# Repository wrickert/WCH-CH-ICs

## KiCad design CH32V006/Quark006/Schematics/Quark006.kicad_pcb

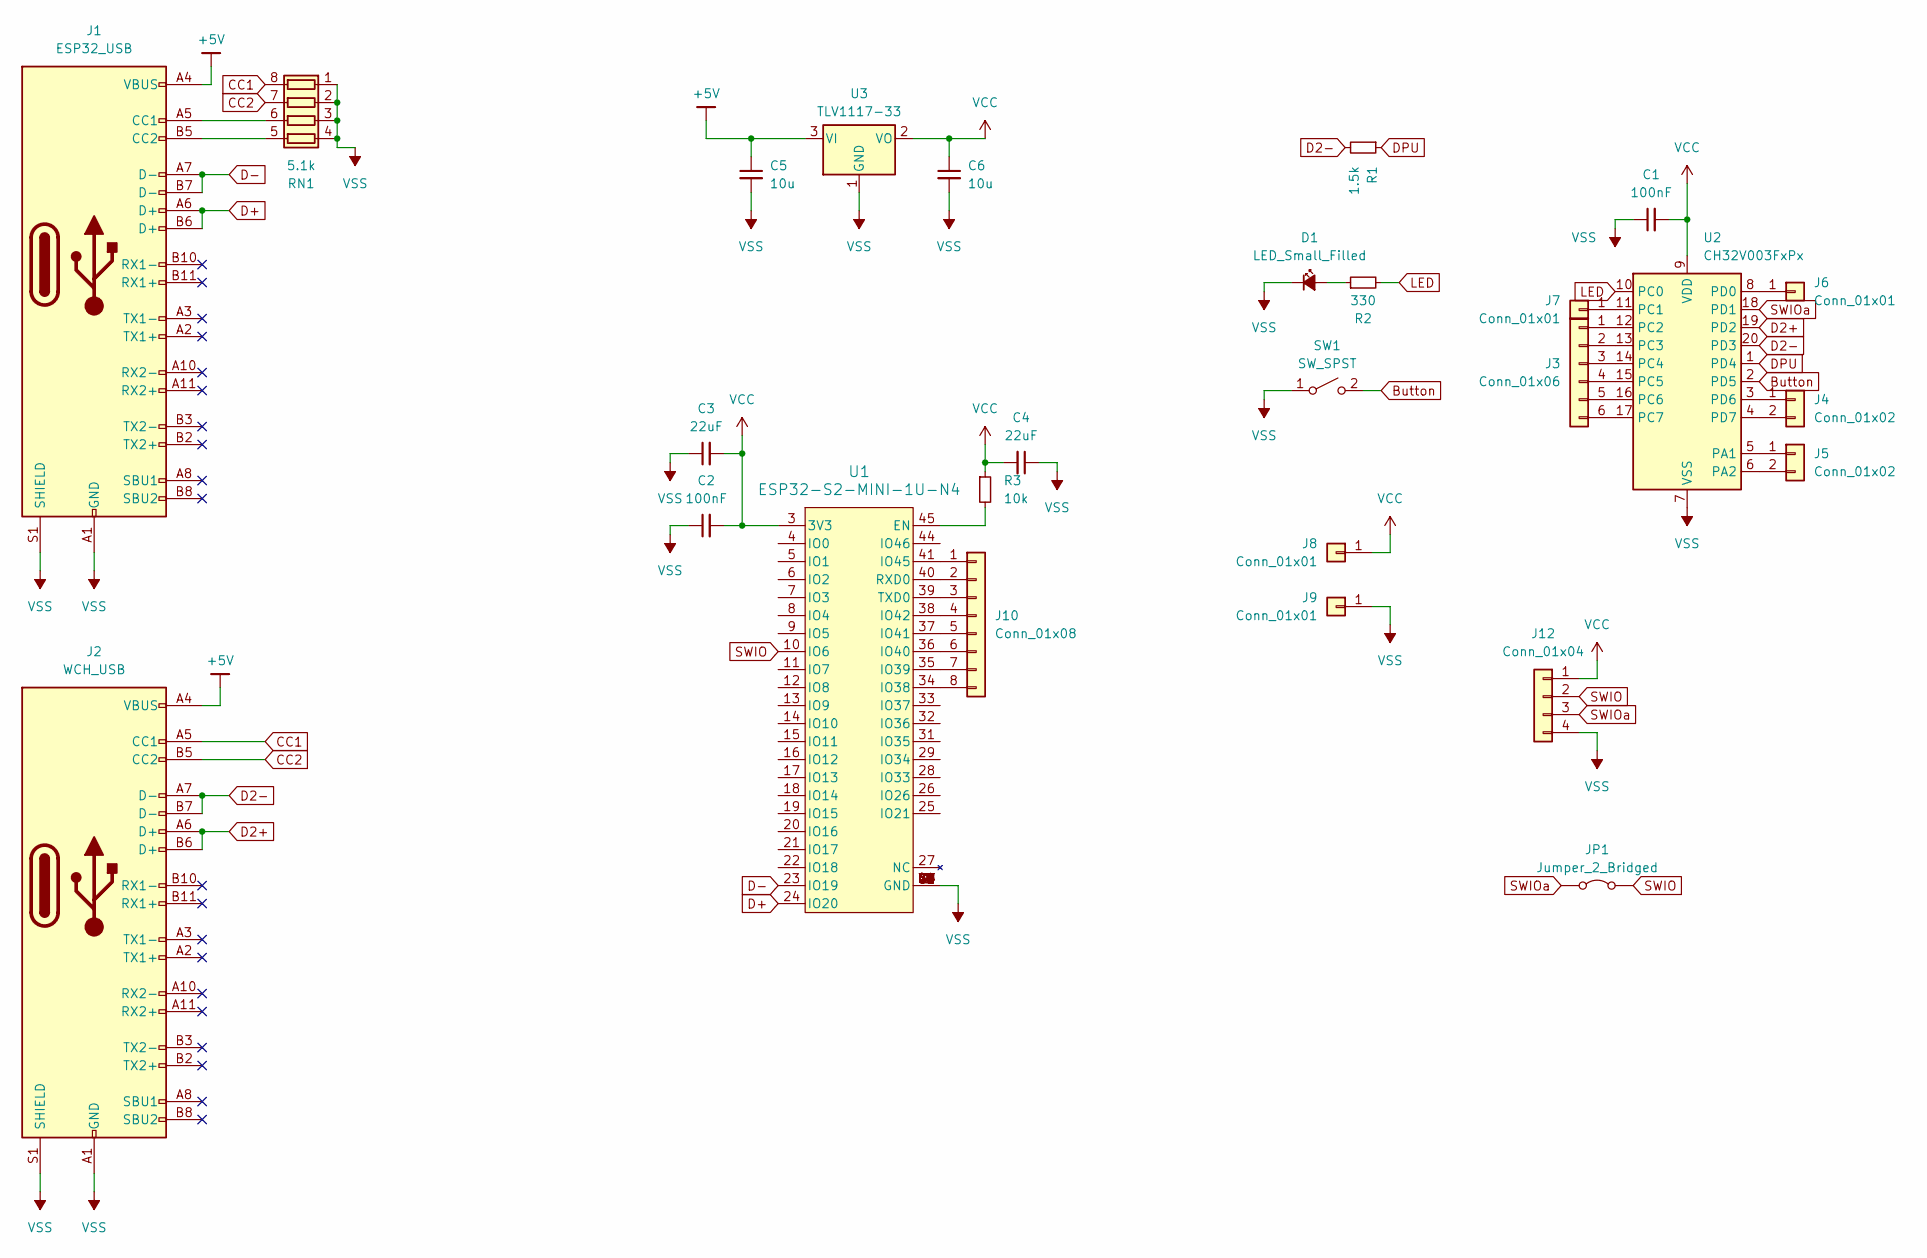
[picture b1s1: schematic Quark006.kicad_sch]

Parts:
C1, C2: 100nF; C_0805_2012Metric
C3, C4: 22uF; C_0805_2012Metric
C5, C6: 10u; C_0805_2012Metric
D1: LED_Small_Filled; LED_0805_2012Metric
J1: ESP32_USB; USB_C_Receptical-Jing
J2: WCH_USB; USB_C_Receptical-Jing
J3: Conn_01x06; PinHeader_1x06_P2.54mm_Vertical
J4, J5: Conn_01x02; PinHeader_1x02_P2.54mm_Vertical
J6, J7, J8, J9: Conn_01x01; PinHeader_1x01_P2.54mm_Vertical
J10: Conn_01x08; PinHeader_1x08_P1.00mm_Vertical
J12: Conn_01x04; PinHeader_1x04_P2.54mm_Vertical
JP1: Jumper_2_Bridged; SolderJumper-2_P1.3mm_Bridged_RoundedPad1.0x1.5mm
R1: 1.5k; R_0805_2012Metric
R2: 330; R_0805_2012Metric
R3: 10k; R_0805_2012Metric
RN1: 5.1k; R_Array_Convex_4x0603
SW1: SW_SPST; TS3315A
U1: ESP32-S2-MINI-1U-N4; ESP32-S2-MINI-1U_EXP
U2: CH32V003FxPx; TSSOP-20_4.4x6.5mm_P0.65mm
U3: TLV1117-33; SOT-223-3_TabPin2

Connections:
+5V: C5.1, J1.A4 (VBUS), J1.A9 (VBUS), J1.B4 (VBUS), J1.B9 (VBUS), J2.A4 (VBUS), J2.A9 (VBUS), J2.B4 (VBUS), J2.B9 (VBUS), U3.3 (VI)
Button: SW1.2 (B), U2.2 (PD5)
CC1: J2.A5 (CC1), RN1.8 (R1.2)
CC2: J2.B5 (CC2), RN1.7 (R2.2)
D2+: J2.A6 (D+), J2.B6 (D+), U2.19 (PD2)
D2-: J2.A7 (D-), J2.B7 (D-), R1.2, U2.20 (PD3)
D+: J1.A6 (D+), J1.B6 (D+), U1.24 (IO20)
D-: J1.A7 (D-), J1.B7 (D-), U1.23 (IO19)
DPU: R1.1, U2.1 (PD4)
LED: R2.2, U2.10 (PC0)
unnamed: D1.2 (A), R2.1
unnamed: J1.A5 (CC1), RN1.6 (R3.2)
unnamed: J1.B5 (CC2), RN1.5 (R4.2)
unnamed: J3.1, U2.12 (PC2)
unnamed: J3.2, U2.13 (PC3)
unnamed: J3.3, U2.14 (PC4)
unnamed: J3.4, U2.15 (PC5)
unnamed: J3.5, U2.16 (PC6)
unnamed: J3.6, U2.17 (PC7)
unnamed: J4.1, U2.3 (PD6)
unnamed: J4.2, U2.4 (PD7)
unnamed: J5.1, U2.5 (PA1)
unnamed: J5.2, U2.6 (PA2)
unnamed: J6.1, U2.8 (PD0)
unnamed: J7.1, U2.11 (PC1)
unnamed: J10.1, U1.41 (IO45)
unnamed: J10.2, U1.40 (RXD0)
unnamed: J10.3, U1.39 (TXD0)
unnamed: J10.4, U1.38 (IO42)
unnamed: J10.5, U1.37 (IO41)
unnamed: J10.6, U1.36 (IO40)
unnamed: J10.7, U1.35 (IO39)
unnamed: J10.8, U1.34 (IO38)
unnamed: R3.2, U1.45 (EN)
SWIO: J12.2, JP1.2 (B), U1.10 (IO6)
SWIOa: J12.3, JP1.1 (A), U2.18 (PD1)
VCC: C1.2, C2.2, C3.2, C4.2, C6.1, J8.1, J12.1, R3.1, U1.3 (3V3), U2.9 (VDD), U3.2 (VO)
VSS: C1.1, C2.1, C3.1, C4.1, C5.2, C6.2, D1.1 (K), J1.A1 (GND), J1.A12 (GND), J1.B1 (GND), J1.B12 (GND), J1.S1 (SHIELD), J2.A1 (GND), J2.A12 (GND), J2.B1 (GND), J2.B12 (GND), J2.S1 (SHIELD), J9.1, J12.4, RN1.1 (R1.1), RN1.2 (R2.1), RN1.3 (R3.1), RN1.4 (R4.1), SW1.1 (A), U1.1 (GND), U1.2 (GND), U1.30 (GND), U1.42 (GND), U1.43 (GND), U1.46 (GND), U1.47 (GND), U1.48 (GND), U1.49 (GND), U1.50 (GND), U1.51 (GND), U1.52 (GND), U1.53 (GND), U1.54 (GND), U1.55 (GND), U1.56 (GND), U1.57 (GND), U1.58 (GND), U1.59 (GND), U1.60 (GND), U1.61 (GND), U1.62 (GND), U1.63 (GND), U1.64 (GND), U1.65 (GND), U1.66 (GND), U1.67 (GND), U1.68 (GND), U1.69 (GND), U1.70 (GND), U1.71 (GND), U1.72 (GND), U1.73 (GND), U2.7 (VSS), U3.1 (GND)

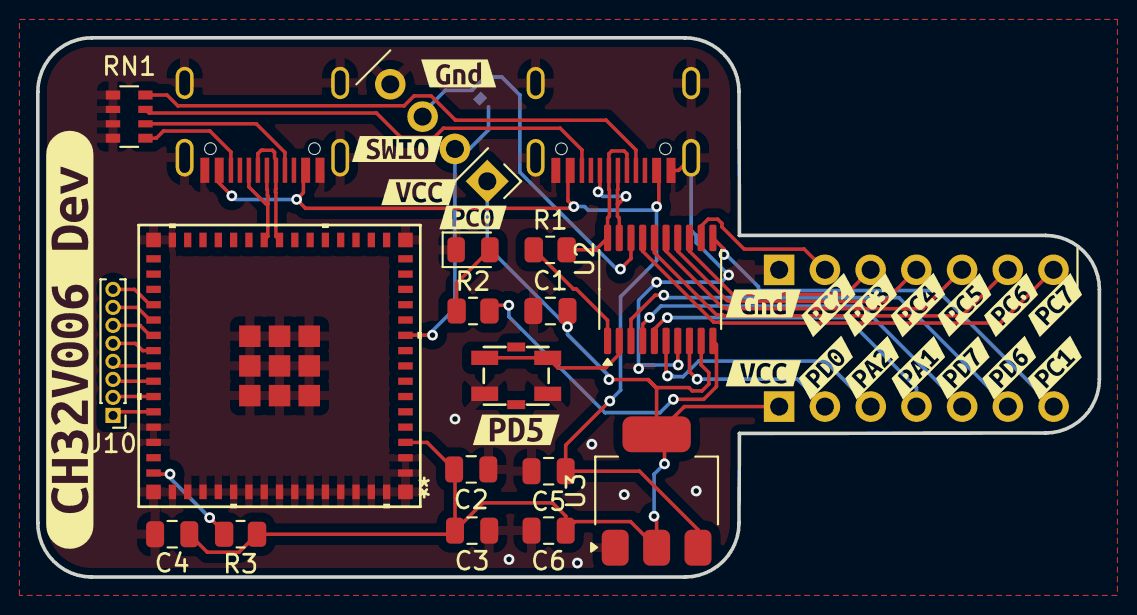
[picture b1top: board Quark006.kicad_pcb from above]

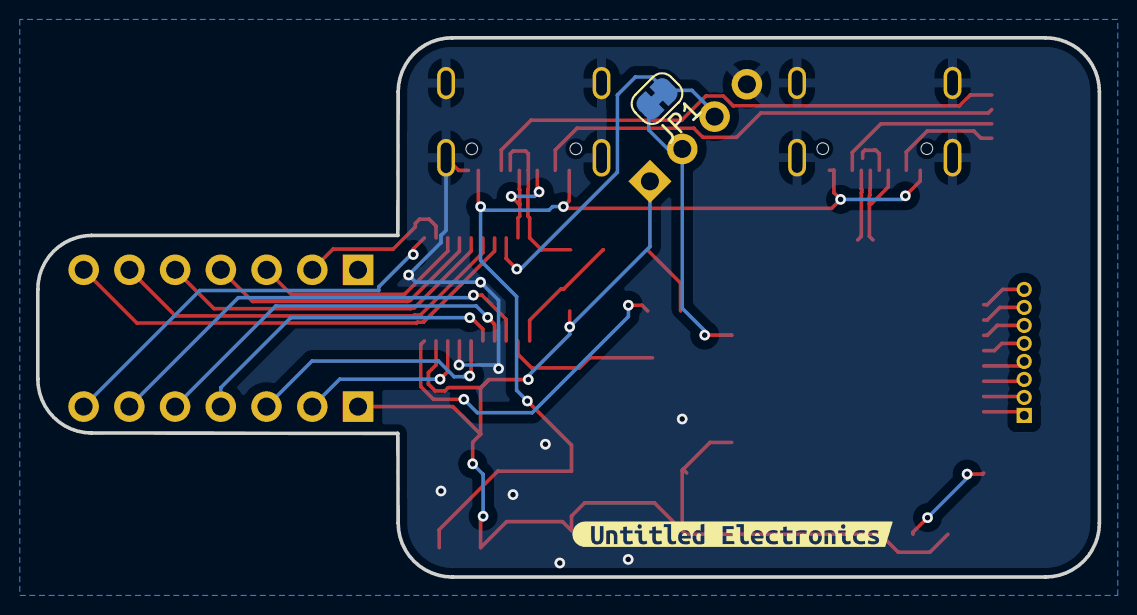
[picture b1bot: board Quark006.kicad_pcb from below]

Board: 2 copper layers, 59.0 x 30.0 mm, 48 parts (2 on the bottom side), 38 nets.

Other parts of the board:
kibuzzard-67AFB7A0: G***; kibuzzard-67AFB7A0
kibuzzard-67AFB7A5: G***; kibuzzard-67AFB7A5
kibuzzard-67AFB7AA: G***; kibuzzard-67AFB7AA
kibuzzard-67AFB7B7: G***; kibuzzard-67AFB7B7
kibuzzard-67AFB7C4: G***; kibuzzard-67AFB7C4
kibuzzard-67AFB7CD: G***; kibuzzard-67AFB7CD
kibuzzard-67AFB7D5: G***; kibuzzard-67AFB7D5
kibuzzard-67AFB7DD: G***; kibuzzard-67AFB7DD
kibuzzard-67AFB7E3: G***; kibuzzard-67AFB7E3
kibuzzard-67AFB7EB: G***; kibuzzard-67AFB7EB
kibuzzard-67AFB7F1: G***; kibuzzard-67AFB7F1
kibuzzard-67AFB7F8, kibuzzard-67AFB7F8#2: G***; kibuzzard-67AFB7F8
kibuzzard-67AFB81A: G***; kibuzzard-67AFB81A
kibuzzard-67AFB799: G***; kibuzzard-67AFB799
kibuzzard-67AFBA81: G***; kibuzzard-67AFBA81
kibuzzard-67AFBDD6: G***; kibuzzard-67AFBDD6
kibuzzard-67AFBE16: G***; kibuzzard-67AFBE16
kibuzzard-67B101C4: G***; kibuzzard-67B101C4
kibuzzard-67B102C6: G***; kibuzzard-67B102C6
kibuzzard-67B10245: G***; kibuzzard-67B10245

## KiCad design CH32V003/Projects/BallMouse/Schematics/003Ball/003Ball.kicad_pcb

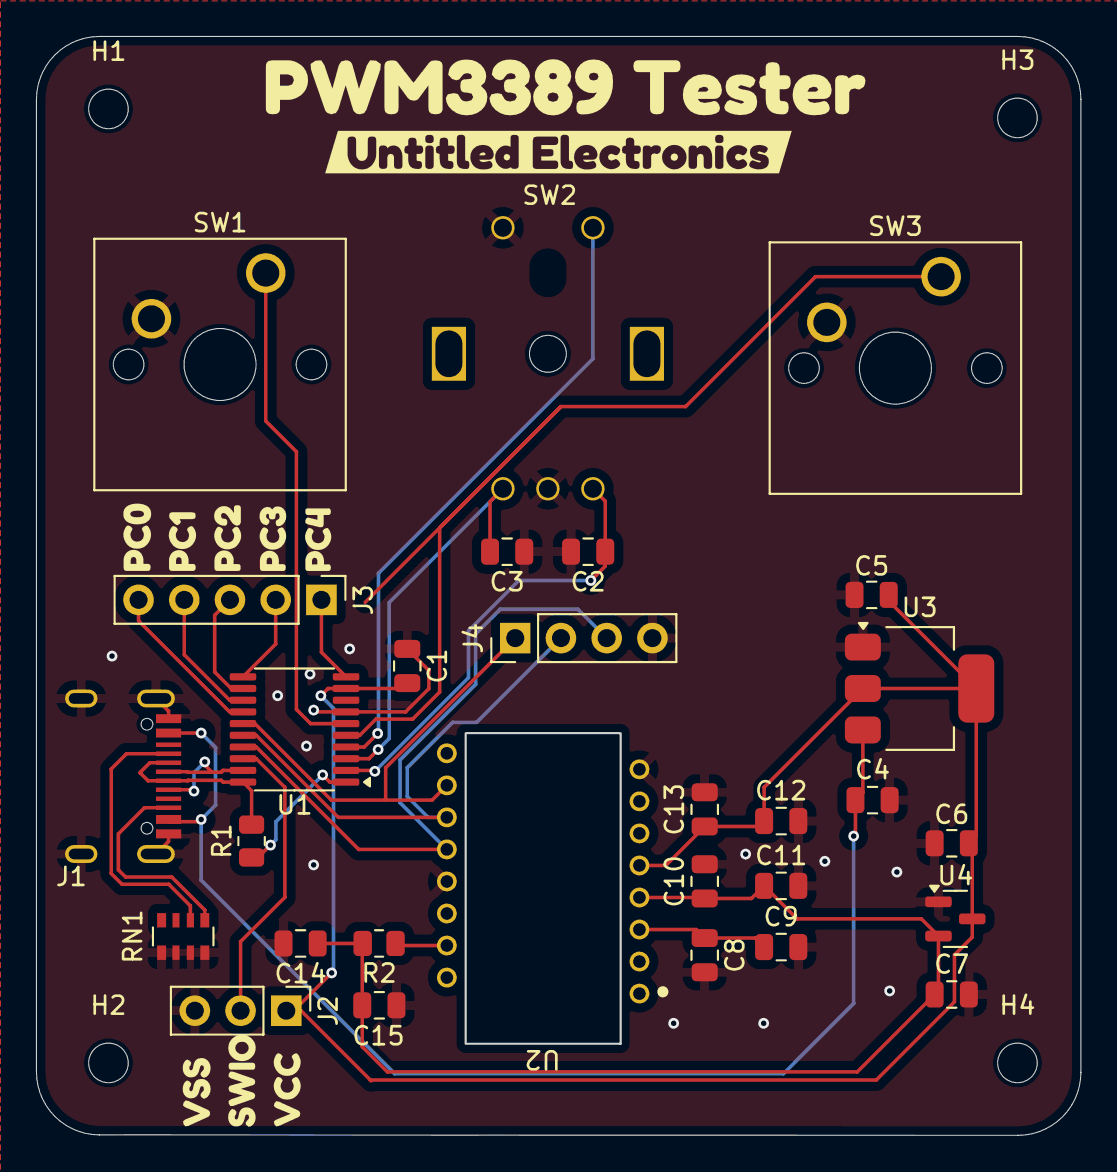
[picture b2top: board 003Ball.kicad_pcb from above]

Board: 2 copper layers, 58.0 x 61.1 mm, 37 parts (0 on the bottom side), 25 nets.

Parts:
C1, C2, C3, C9, C10, C12, C14: 100nF; C_0805_2012Metric
C4, C5: 10u; C_0805_2012Metric
C6, C7: 1uF; C_0805_2012Metric
C8: 4.7uF; C_0805_2012Metric
C11, C13, C15: 10uF; C_0805_2012Metric
H1, H2, H3, H4: MountingHole; MountingHole_2.2mm_M2
J1: USB_C_Receptacle; USB_C_Receptical-Jing
J2: Prog; PinHeader_1x03_P2.54mm_Vertical
J3: Conn_01x05; PinHeader_1x05_P2.54mm_Vertical
J4: Conn_01x04; PinHeader_1x04_P2.54mm_Vertical
R1: 1.5k; R_0805_2012Metric
R2: 13; R_0805_2012Metric
RN1: 5.1k; R_Array_Convex_4x0603
SW1, SW3: SW_Push_45deg; SW_Cherry_MX_1.00u_PCB
SW2: Rotary_Encoder_Switch; EC11L1524E03_Rotary_Encoder
U1: CH32V003FxPx; TSSOP-20_4.4x6.5mm_P0.65mm
U2: PWM3389; PMW3389
U3: TLV1117-33; SOT-223-3_TabPin2
U4: TLV1117-18; SOT-23
kibuzzard-67733B6F: G***; kibuzzard-67733B6F
kibuzzard-67733BE6: G***; kibuzzard-67733BE6
kibuzzard-67733C4A: G***; kibuzzard-67733C4A
kibuzzard-67733C22: G***; kibuzzard-67733C22

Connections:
+1V8: C7.1, C10.1, C11.1, C14.1, C15.1, R2.2, U2.4 (VCC), U4.2 (VO)
+5V: C4.1, J1.A4 (VBUS), J1.A9 (VBUS), J1.B4 (VBUS), J1.B9 (VBUS), U3.3 (VI)
/RotaryA: C2.1, SW2.B, U1.2 (PD5)
/RotaryB: C3.2, SW2.A, U1.3 (PD6)
/RotaryS: SW2.S2, U1.4 (PD7)
D+: J1.A6 (D+), J1.B6 (D+), U1.19 (PD2)
D-: J1.A7 (D-), J1.B7 (D-), R1.2, U1.20 (PD3)
DPU: R1.1, U1.1 (PD4)
Left: SW1.1, U1.6 (PA2)
MISO: J4.3, U1.17 (PC7), U2.12 (MISO)
MOSI: J4.2, U1.16 (PC6), U2.11 (MOSI)
unnamed: J1.A5 (CC1), RN1.6 (R3.2)
unnamed: J1.B5 (CC2), RN1.5 (R4.2)
unnamed: J3.1, U1.10 (PC0)
unnamed: J3.2, U1.11 (PC1)
unnamed: J3.3, U1.12 (PC2)
unnamed: J3.4, U1.13 (PC3)
unnamed: J3.5, U1.14 (PC4)
unnamed: R2.1, U2.15 (LED)
unnamed: C8.1, C9.1, U2.3 (VDCPix)
Right: SW3.1, U1.5 (PA1)
SCLK: J4.1, U1.15 (PC5), U2.10 (SCLK)
SWIO: J2.2, U1.18 (PD1)
VCC: C1.2, C5.1, C6.1, C12.1, C13.1, J2.1, U1.9 (VDD), U2.5 (VDDIO), U3.2 (VO), U4.3 (VI)
VSS: C1.1, C2.2, C3.1, C4.2, C5.2, C6.2, C7.2, C8.2, C9.2, C10.2, C11.2, C12.2, C13.2, C14.2, C15.2, J1.A1 (GND), J1.A12 (GND), J1.B1 (GND), J1.B12 (GND), J1.S1 (SHIELD), J2.3, J4.4, RN1.1 (R1.1), RN1.2 (R2.1), RN1.3 (R3.1), RN1.4 (R4.1), SW1.2, SW2.C, SW2.S1, SW3.2, U1.7 (VSS), U2.8 (VSS), U2.13 (NCS), U3.1 (GND), U4.1 (GND)

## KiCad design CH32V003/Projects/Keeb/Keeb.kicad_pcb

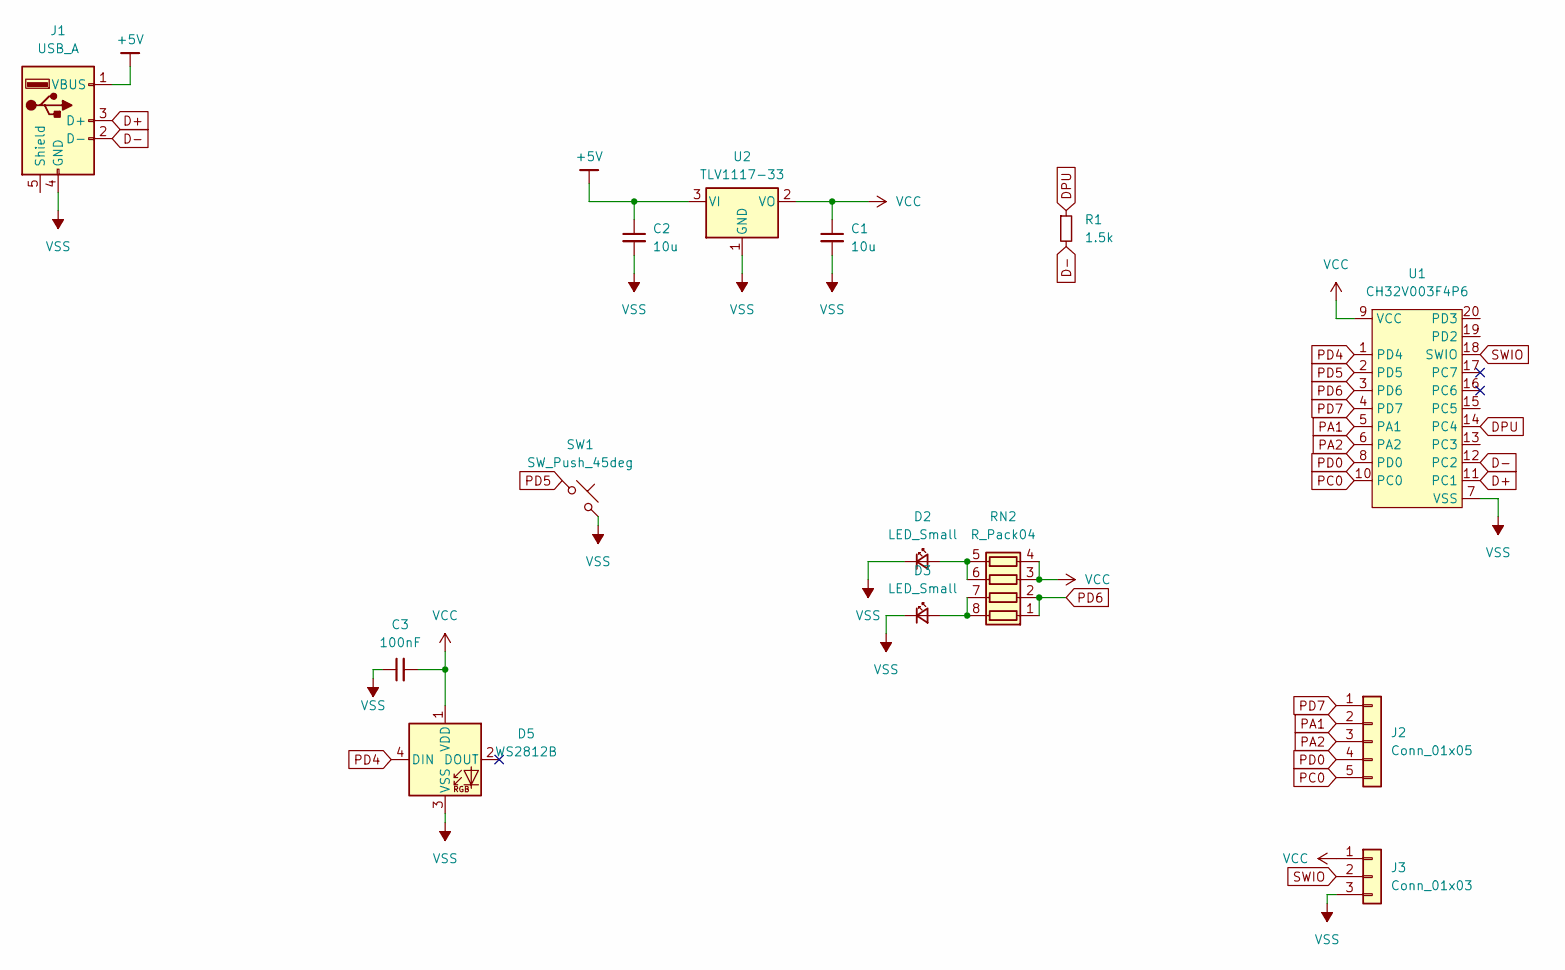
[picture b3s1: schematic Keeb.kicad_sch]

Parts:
C1, C2: 10u; C_0805_2012Metric
C3: 100nF; C_0805_2012Metric
D2, D3: LED_Small; LED_0805_2012Metric
D5: WS2812B; SK6812-E_Reverse
J1: USB_A; CONN-USB-A-PCB-TRACES
J2: Conn_01x05; PinHeader_1x05_P2.54mm_Vertical
J3: Conn_01x03; PinHeader_1x03_P2.54mm_Vertical
R1: 1.5k; R_0805_2012Metric
RN2: R_Pack04; R_Array_Convex_4x0603
SW1: SW_Push_45deg; SW_Cherry_MX_1.00u_PCB
U1: CH32V003F4P6; TSSOP-20_4.4x6.5mm_P0.65mm
U2: TLV1117-33; SOT-23-3

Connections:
+5V: C2.1, J1.1 (VBUS), U2.3 (VI)
D+: J1.3 (D+), U1.11 (PC1)
D-: J1.2 (D-), R1.2, U1.12 (PC2)
DPU: R1.1, U1.14 (PC4)
unnamed: D2.2 (A), RN2.5 (R4.2), RN2.6 (R3.2)
unnamed: D3.2 (A), RN2.7 (R2.2), RN2.8 (R1.2)
PA1: J2.2, U1.5 (PA1)
PA2: J2.3, U1.6 (PA2)
PC0: J2.5, U1.10 (PC0)
PD0: J2.4, U1.8 (PD0)
PD4: D5.4 (DIN), U1.1 (PD4)
PD5: SW1.1, U1.2 (PD5)
PD6: RN2.1 (R1.1), RN2.2 (R2.1), U1.3 (PD6)
PD7: J2.1, U1.4 (PD7)
SWIO: J3.2, U1.18 (SWIO)
VCC: C1.1, C3.2, D5.1 (VDD), J3.1, RN2.3 (R3.1), RN2.4 (R4.1), U1.9 (VCC), U2.2 (VO)
VSS: C1.2, C2.2, C3.1, D2.1 (K), D3.1 (K), D5.3 (VSS), J1.4 (GND), J3.3, SW1.2, U1.7 (VSS), U2.1 (GND)

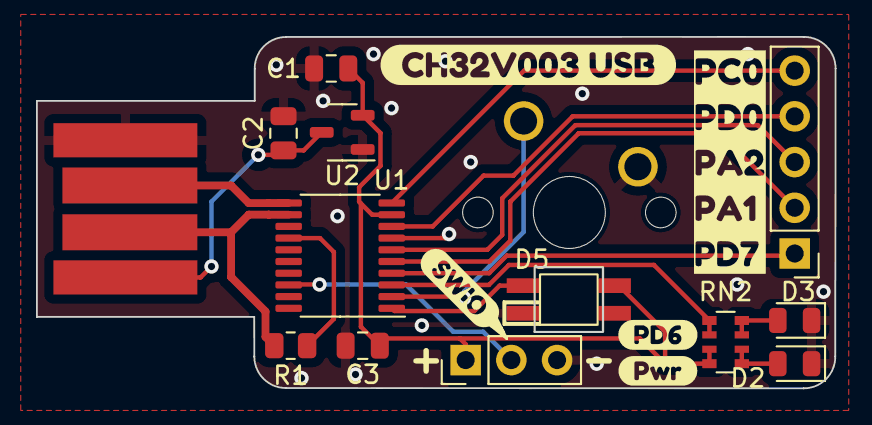
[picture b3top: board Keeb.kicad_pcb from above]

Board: 2 copper layers, 44.4 x 19.5 mm, 19 parts (1 on the bottom side), 17 nets.

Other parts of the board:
kibuzzard-65C27C9E: G***; kibuzzard-65C27C9E
kibuzzard-65C27C56: G***; kibuzzard-65C27C56
kibuzzard-65C27CA6: G***; kibuzzard-65C27CA6
kibuzzard-65C27CFD: G***; kibuzzard-65C27CFD
kibuzzard-65C28AFE: G***; kibuzzard-65C28AFE

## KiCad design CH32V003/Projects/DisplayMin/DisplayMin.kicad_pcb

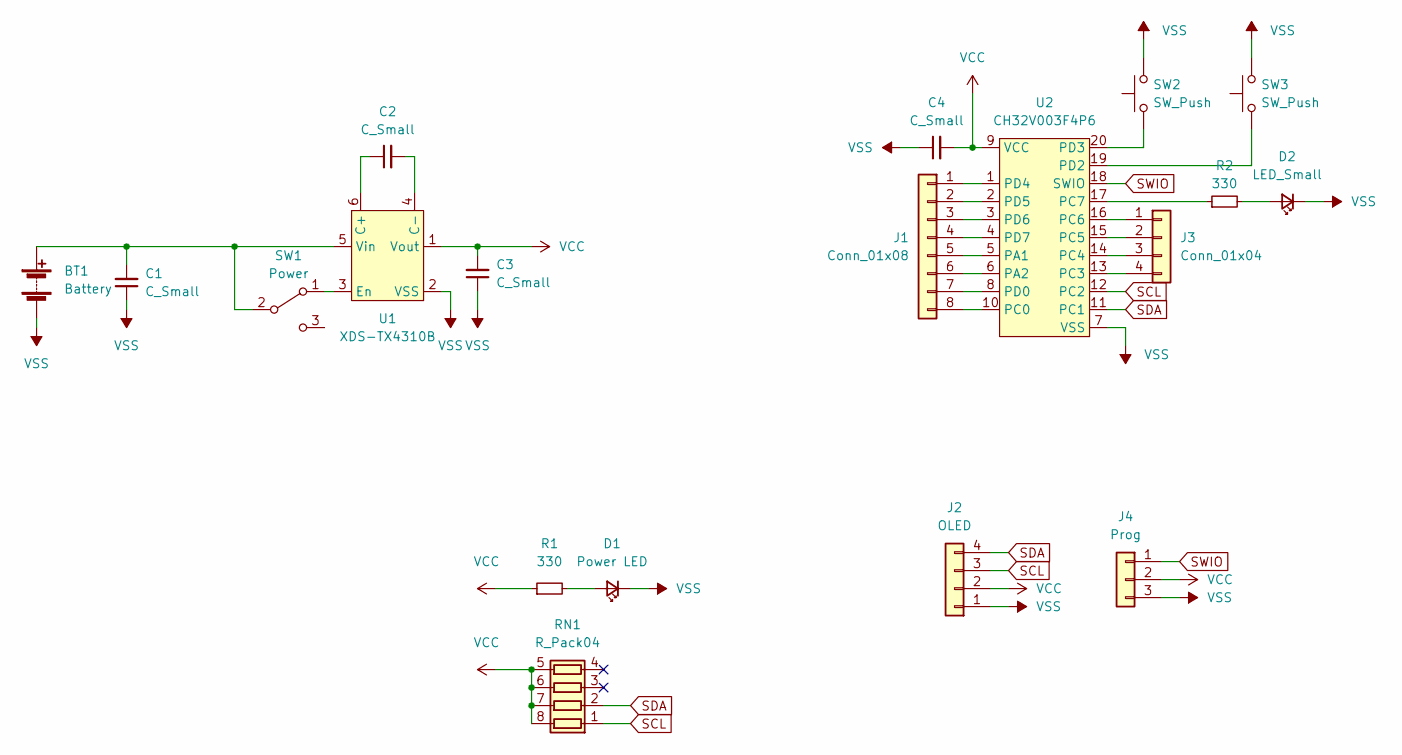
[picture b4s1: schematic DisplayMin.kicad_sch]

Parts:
BT1: Battery; Keystone_1012_2AA_SMD_UE
C1, C2, C3, C4: C_Small; C_0805_2012Metric
D1: Power LED; LED_0805_2012Metric
D2: LED_Small; LED_0805_2012Metric
J1: Conn_01x08; PinHeader_1x08_P2.54mm_Vertical
J2: OLED; PinHeader_1x04_P2.54mm_Vertical
J3: Conn_01x04; PinHeader_1x04_P2.54mm_Vertical
J4: Prog; PinHeader_1x03_P2.54mm_Vertical
R1, R2: 330; R_0805_2012Metric
RN1: R_Pack04; R_Array_Concave_4x0603
SW1: Power; SK-3296S_switch
SW2: SW_Push; SW_SPST_EVQP0
SW3: SW_Push; SW_Cherry_MX_1.00u_PCB
U1: XDS-TX4310B; SOT-23-6
U2: CH32V003F4P6; SSOP-20_4.4x6.5mm_P0.65mm

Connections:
unnamed: BT1.1 (+), C1.2, SW1.2 (B), U1.5 (Vin)
unnamed: C2.1, U1.6 (C+)
unnamed: C2.2, U1.4 (C-)
unnamed: D1.2 (A), R1.2
unnamed: D2.2 (A), R2.2
unnamed: J1.1, U2.1 (PD4)
unnamed: J1.2, U2.2 (PD5)
unnamed: J1.3, U2.3 (PD6)
unnamed: J1.4, U2.4 (PD7)
unnamed: J1.5, U2.5 (PA1)
unnamed: J1.6, U2.6 (PA2)
unnamed: J1.7, U2.8 (PD0)
unnamed: J1.8, U2.10 (PC0)
unnamed: J3.1, U2.16 (PC6)
unnamed: J3.2, U2.15 (PC5)
unnamed: J3.3, U2.14 (PC4)
unnamed: J3.4, U2.13 (PC3)
unnamed: R2.1, U2.17 (PC7)
unnamed: SW2.1, U2.20 (PD3)
unnamed: SW3.1, U2.19 (PD2)
unnamed: SW1.1 (A), U1.3 (En)
SCL: J2.3, RN1.1 (R1.1), U2.12 (PC2)
SDA: J2.4, RN1.2 (R2.1), U2.11 (PC1)
SWIO: J4.1, U2.18 (SWIO)
VCC: C3.2, C4.2, J2.2, J4.2, R1.1, RN1.5 (R4.2), RN1.6 (R3.2), RN1.7 (R2.2), RN1.8 (R1.2), U1.1 (Vout), U2.9 (VCC)
VSS: BT1.2 (-), C1.1, C3.1, C4.1, D1.1 (K), D2.1 (K), J2.1, J4.3, SW2.2, SW3.2, U1.2 (VSS), U2.7 (VSS)

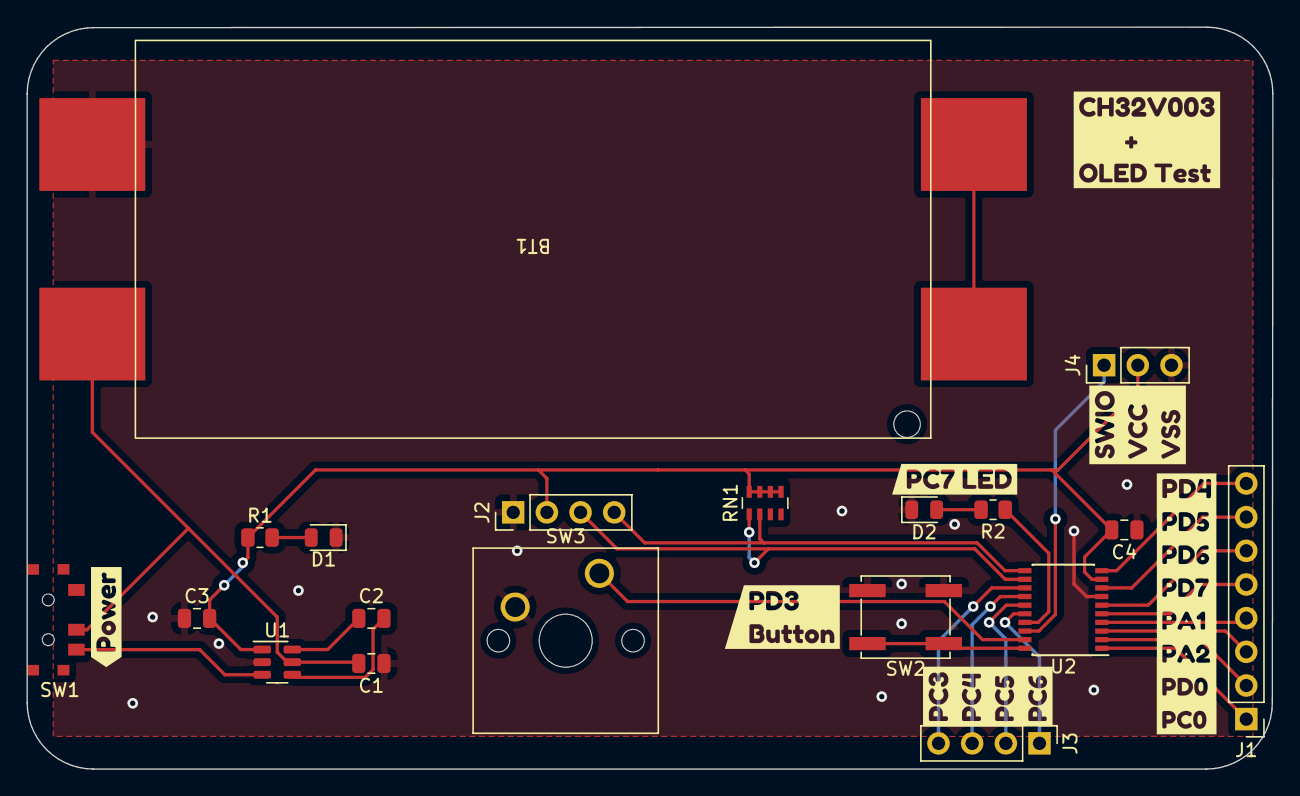
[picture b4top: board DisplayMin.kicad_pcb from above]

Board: 2 copper layers, 94.0 x 56.0 mm, 27 parts (1 on the bottom side), 26 nets.

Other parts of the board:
Ref**: Val**; UELogoAbove
kibuzzard-63E932A7: G***; kibuzzard-63E932A7
kibuzzard-63E932E7: G***; kibuzzard-63E932E7
kibuzzard-63E933A2: G***; kibuzzard-63E933A2
kibuzzard-63E934AF: G***; kibuzzard-63E934AF
kibuzzard-63E9336F: G***; kibuzzard-63E9336F
kibuzzard-63E93344: G***; kibuzzard-63E93344
kibuzzard-63E93477: G***; kibuzzard-63E93477

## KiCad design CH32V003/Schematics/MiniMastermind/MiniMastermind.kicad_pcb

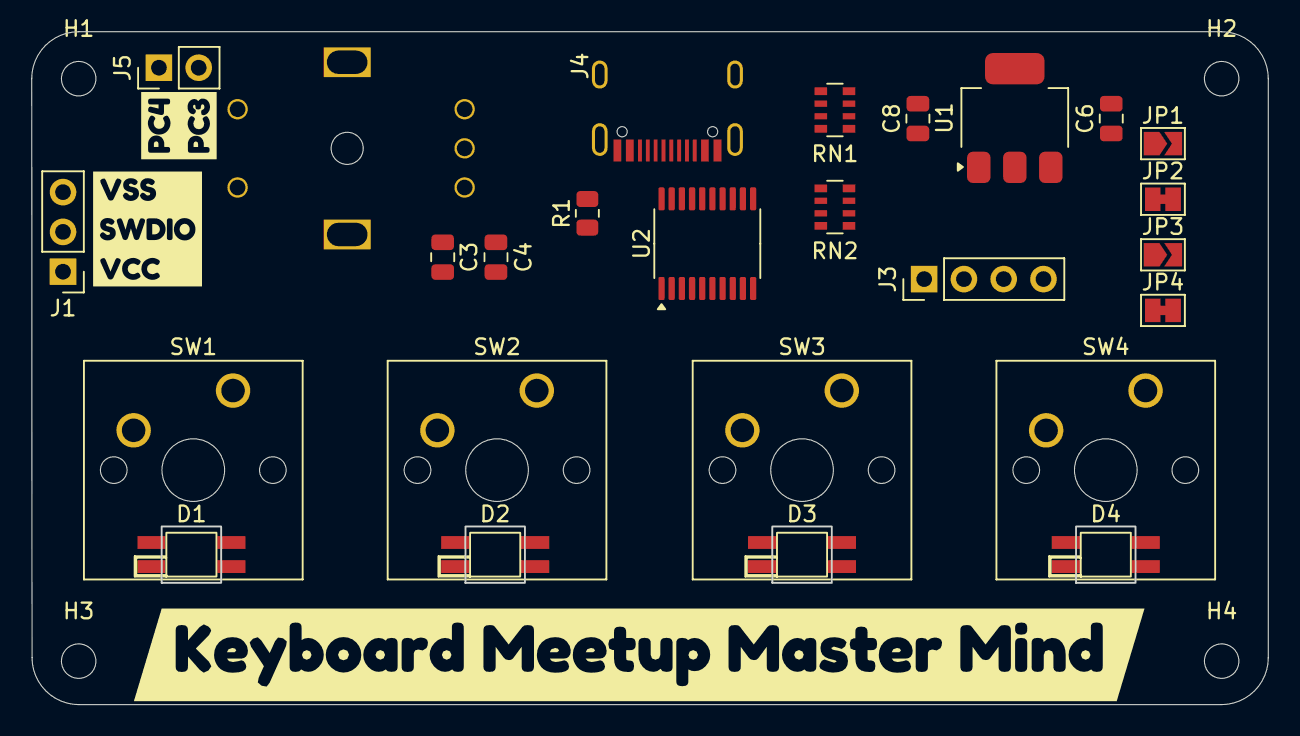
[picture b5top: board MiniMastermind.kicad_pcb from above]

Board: 2 copper layers, 79.0 x 43.0 mm, 33 parts (0 on the bottom side), 24 nets, no tracks yet.

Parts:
C3, C4: 100nF; C_0805_2012Metric
C6, C8: 10u; C_0805_2012Metric
D1, D2, D3, D4: WS2812B; SK6812-E_Reverse
H1, H2, H3, H4: MountingHole; MountingHole_2.2mm_M2
J1: Prog; PinHeader_1x03_P2.54mm_Vertical
J3: OledDisplay; PinHeader_1x04_P2.54mm_Vertical
J4: USB_C_Receptacle; USB_C_Receptical-Jing
J5: Conn_01x02; PinHeader_1x02_P2.54mm_Vertical
JP1: JOpen; SolderJumper-2_P1.3mm_Open_TrianglePad1.0x1.5mm
JP2: JClosed; SolderJumper-2_P1.3mm_Bridged_Pad1.0x1.5mm
JP3: Jumper_2_Open; SolderJumper-2_P1.3mm_Open_TrianglePad1.0x1.5mm
JP4: Jumper_2_Bridged; SolderJumper-2_P1.3mm_Bridged_Pad1.0x1.5mm
R1: 1.5k; R_0805_2012Metric
RN1, RN2: 5.1k; R_Array_Convex_4x0603
SW1, SW3, SW4: SW_Push_45deg; SW_Cherry_MX_1.00u_PCB
SW2: Rotary_Encoder_Switch; SW_Cherry_MX_1.00u_PCB
SW5: SW_Push_45deg; EC11L1524E03_Rotary_Encoder
U1: TLV1117-33; SOT-223-3_TabPin2
U2: CH32V003F4P6; TSSOP-20_4.4x6.5mm_P0.65mm
kibuzzard-65F8A563: G***; kibuzzard-65F8A563
kibuzzard-65F8A587: G***; kibuzzard-65F8A587
kibuzzard-65F8A704: G***; kibuzzard-65F8A704

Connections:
+5V: C6.1, D1.2 (VDD), D2.2 (VDD), D3.2 (VDD), D4.2 (VDD), J4.A4 (VBUS), J4.A9 (VBUS), J4.B4 (VBUS), J4.B9 (VBUS), U1.3 (VI)
/RotaryA: C3.1, U2.8 (PD0)
/RotaryB: C4.2, U2.10 (PC0)
D+: J4.A6 (D+), J4.B6 (D+), U2.19 (PD2)
D-: J4.A7 (D-), J4.B7 (D-), R1.2, U2.20 (PD3)
DPU: R1.1, U2.1 (PD4)
unnamed: D1.3 (DOUT), D2.1 (DIN)
unnamed: D2.3 (DOUT), D3.1 (DIN)
unnamed: D3.3 (DOUT), D4.1 (DIN)
unnamed: J3.3, JP3.2 (B), JP4.1 (A)
unnamed: J3.4, JP1.2 (B), JP2.2 (B)
unnamed: J4.A5 (CC1), RN1.6 (R3.2)
unnamed: J4.B5 (CC2), RN1.5 (R4.2)
PA2: D1.1 (DIN), U2.6 (PA2)
PC3: J5.2, U2.13 (PC3)
PC4: J5.1, U2.14 (PC4)
PD5: SW1.1, U2.2 (PD5)
PD6: SW3.1, U2.3 (PD6)
PD7: SW4.1, U2.4 (PD7)
SCL: J3.2, RN2.3 (R3.1), U2.12 (PC2), U2.15 (PC5)
SDA: J3.1, RN2.4 (R4.1), U2.11 (PC1), U2.16 (PC6)
SWIO: J1.2, U2.18 (SWIO)
VCC: C8.1, J1.1, JP1.1 (A), JP4.2 (B), RN2.5 (R4.2), RN2.6 (R3.2), U1.2 (VO), U2.9 (VCC)
VSS: C3.2, C4.1, C6.2, C8.2, D1.4 (VSS), D2.4 (VSS), D3.4 (VSS), D4.4 (VSS), J1.3, J4.A1 (GND), J4.A12 (GND), J4.B1 (GND), J4.B12 (GND), J4.S1 (SHIELD), JP2.1 (A), JP3.1 (A), RN1.1 (R1.1), RN1.2 (R2.1), RN1.3 (R3.1), RN1.4 (R4.1), SW1.2, SW3.2, SW4.2, U1.1 (GND), U2.7 (VSS)

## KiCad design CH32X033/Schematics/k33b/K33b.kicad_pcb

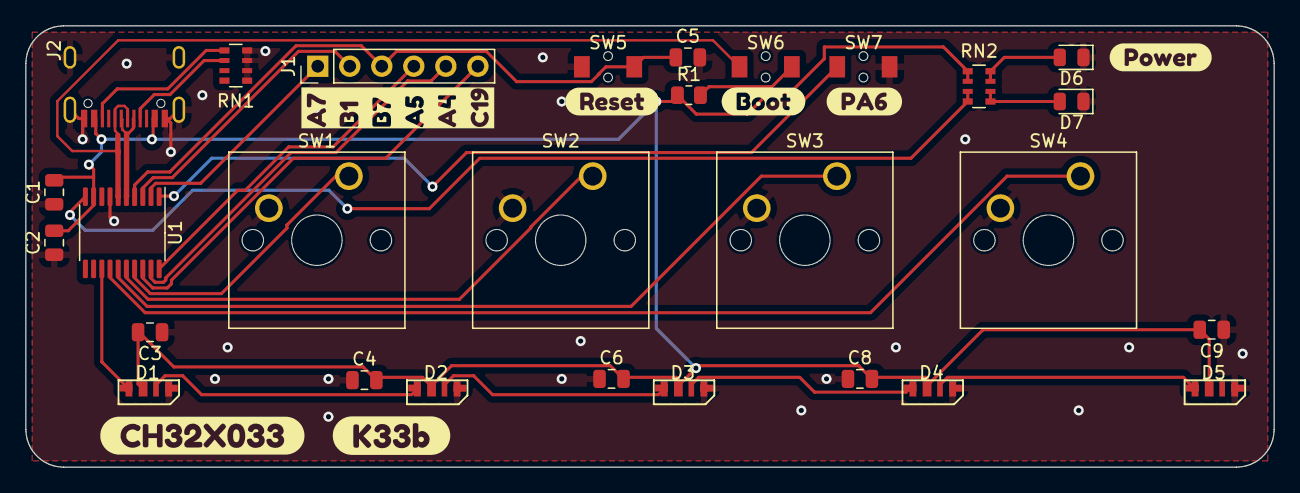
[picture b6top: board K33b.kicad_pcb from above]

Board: 2 copper layers, 99.0 x 35.0 mm, 35 parts (0 on the bottom side), 26 nets.

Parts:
C1: 4.7uF; C_0805_2012Metric
C2, C3, C4, C5, C6, C8, C9: 100nF; C_0805_2012Metric
D1, D2, D3, D4, D5: WS2812B; SK6812SIDE-A-RVS
D6, D7: LED_Small; LED_0805_2012Metric
J1: Conn_01x06; PinHeader_1x06_P2.54mm_Vertical
J2: USB_C_Receptacle; USB_C_Receptical-Jing
R1: 4k7; R_0805_2012Metric
RN1: 5.1k; R_Array_Convex_4x0603
RN2: R_Pack04; R_Array_Convex_4x0603
SW1, SW2, SW3, SW4: SW_Push_45deg; SW_Cherry_MX_1.00u_PCB
SW5: Reset; TS-1185-C-A-B-B
SW6: Boot; TS-1185-C-A-B-B
SW7: ChKeys; TS-1185-C-A-B-B
U1: CH32X033F8P6; TSSOP-20_4.4x6.5mm_P0.65mm
kibuzzard-65BAAB5D: G***; kibuzzard-65BAAB5D
kibuzzard-65BAAB6D: G***; kibuzzard-65BAAB6D
kibuzzard-65BAAB8A: G***; kibuzzard-65BAAB8A
kibuzzard-65BAAF54: G***; kibuzzard-65BAAF54
kibuzzard-65BAAF97: G***; kibuzzard-65BAAF97
kibuzzard-65BAB00C: G***; kibuzzard-65BAB00C
kibuzzard-65BAB04D: G***; kibuzzard-65BAB04D

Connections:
+5V: C1.2, C2.2, C3.2, C4.2, C6.2, C8.2, C9.2, D1.2 (VDD), D2.2 (VDD), D3.2 (VDD), D4.2 (VDD), D5.2 (VDD), J2.A4 (VBUS), J2.A9 (VBUS), J2.B4 (VBUS), J2.B9 (VBUS), R1.1, RN2.1 (R1.1), RN2.2 (R2.1), U1.9 (VCC)
D+: J2.A6 (D+), J2.B6 (D+), SW6.1, U1.6 (PC17)
D-: J2.A7 (D-), J2.B7 (D-), U1.5 (PC16)
unnamed: D1.3 (DOUT), D2.1 (DIN)
unnamed: D2.3 (DOUT), D3.1 (DIN)
unnamed: D3.3 (DOUT), D4.1 (DIN)
unnamed: D4.3 (DOUT), D5.1 (DIN)
unnamed: D6.2 (A), RN2.7 (R2.2), RN2.8 (R1.2)
unnamed: D7.2 (A), RN2.5 (R4.2), RN2.6 (R3.2)
unnamed: J2.A5 (CC1), RN1.6 (R3.2)
unnamed: J2.B5 (CC2), RN1.5 (R4.2)
unnamed: R1.2, SW6.2
PA0: SW4.1, U1.14 (PA0)
PA1: SW3.1, U1.15 (PA1)
PA2: SW2.1, U1.16 (PA2)
PA3: SW1.1, U1.17 (PA3)
PA4: J1.5, U1.19 (PA4)
PA5: J1.4, U1.20 (PA5)
PA6: SW7.1, U1.1 (PA6)
PA7: J1.1, U1.2 (PA7)
PA9: RN2.3 (R3.1), RN2.4 (R4.1), U1.10 (PA9)
PB1: J1.2, U1.3 (PB1)
PB7: C5.1, J1.3, SW5.2, U1.4 (PB7)
PC3: D1.1 (DIN), U1.13 (PC3)
PC19: J1.6, U1.18 (PC19)
VSS: C1.1, C2.1, C3.1, C4.1, C5.2, C6.1, C8.1, C9.1, D1.4 (VSS), D2.4 (VSS), D3.4 (VSS), D4.4 (VSS), D5.4 (VSS), D6.1 (K), D7.1 (K), J2.A1 (GND), J2.A12 (GND), J2.B1 (GND), J2.B12 (GND), J2.S1 (SHIELD), RN1.1 (R1.1), RN1.2 (R2.1), RN1.3 (R3.1), RN1.4 (R4.1), SW1.2, SW2.2, SW3.2, SW4.2, SW5.1, SW7.2, U1.7 (VSS)

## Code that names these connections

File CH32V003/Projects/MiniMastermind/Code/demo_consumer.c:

#include "ch32v003fun.h"
#include <stdio.h>
#include <string.h>
#include <stdbool.h>
#include "rv003usb.h"

uint32_t  timer = 0;
#define DEBOUNCE_TIME 50 // Debounce time in milliseconds
uint8_t buttons = 0;

// Define states for the state machine
typedef enum {
    RELEASED,
    MAYBE_PRESSED,
    PRESSED,
    MAYBE_RELEASED
} ButtonState;

int main()
{
	SystemInit();
	Delay_Ms(1); // Ensures USB re-enumeration after bootloader or reset; Spec demand >2.5µs ( TDDIS )
	usb_setup();

   funGpioInitAll();
   funPinMode( PD5, GPIO_CFGLR_IN_PUPD);
   funDigitalWrite( PD5, true);
   funPinMode( PD6, GPIO_CFGLR_IN_PUPD);
   funDigitalWrite( PD6, true);
   funPinMode( PD7, GPIO_CFGLR_IN_PUPD);
   funDigitalWrite( PD7, true);
   funPinMode( PA1, GPIO_CFGLR_IN_PUPD);
   funDigitalWrite( PA1, true);
   
   static uint32_t lastTimer = 0;
     
    ButtonState currentState = RELEASED;
    bool buttonPressed = false;

	while(1){
		bool buttonState = !funDigitalRead(PD5);         
      
      if(buttonState){
         buttons = 1;
         led();
         }


/*
        // State machine logic
        switch (currentState) {
            case RELEASED:
                if (buttonState) {
                    currentState = MAYBE_PRESSED;
							Delay_Ms(1000);
                }
                break;
            case MAYBE_PRESSED:
                if (buttonState) {
                    currentState = PRESSED;
                    buttonPressed = true;
                } else {
                    currentState = RELEASED;
                }
                break;
            case PRESSED:
                if (!buttonState) {
                    currentState = MAYBE_RELEASED;
							Delay_Ms(1000);
                }
                break;
            case MAYBE_RELEASED:
                if (!buttonState) {
                    currentState = RELEASED;
                    buttonPressed = false;
                } else {
                    currentState = PRESSED;
                }
                break;
        }

        // Button action when pressed
        if (buttonPressed) {

         buttons |= 0b10000000;
			}

			Delay_Ms(12600);
}
 */      

   }
}

void led(){
   
   funPinMode( PC2,  GPIO_Speed_10MHz | GPIO_CNF_OUT_PP );
   funDigitalWrite( PC2, true);
         funDigitalWrite( PC2, FUN_LOW);
}

void usb_handle_user_in_request( struct usb_endpoint * e, uint8_t * scratchpad, int endp, uint32_t sendtok, struct rv003usb_internal * ist )
{

	if (endp ==1) {
		// If it's a data endpoint (not control), handle consumer control data
		static uint8_t consumer_data[1] = { 0x00};//, 0x00};//, 0x00, 0x00}; // Placeholder data

      if(buttons){
         led();
         consumer_data[0] = 0x02;
         buttons = 0;
      }
		

		// Modify consumer_data array to represent consumer control data
		// For example, to adjust volume, you would change the second byte (0x00) to represent the volume level
		
/*      
      if(buttons & 0b10000000){
				consumer_data[0] = 0x01;
		}
      else if(buttons & 0b01000000){
         consumer_data[0] = 0x02;
		}	
      else if(buttons & 0b00100000){
         consumer_data[0] = 0x04;
		}	
      else if(buttons & 0b00010000){
         consumer_data[0] = 0x08;
		}	
		else{
			consumer_data[0] = 0x00;
         buttons = 0;
		}
	
*/


		// Send consumer data
		usb_send_data(consumer_data, sizeof(consumer_data), 0, sendtok);
	 } 

	else {
	  // If it's a control transfer, NAK it.
	  usb_send_empty(sendtok);
 }
}

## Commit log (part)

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2023-02-07 Updating for hondouras trip
2023-02-12 003 dev board with display closer
2024-01-26 Created Keeb
2024-02-09 Ordered Keeb and K33b
2024-02-22 Added CH32V103
2024-03-06 Added dev boards
2024-03-15 Assembled K33b and Keeb.
2024-03-18 Started mini mastermind
2024-03-19 Ordering Master Mind
2024-04-03 code progress
2024-04-04 added consumer
2024-04-05 blarg
2024-04-05 Closer but I need to move button handling out of the handle_user_in_request
2024-04-26 Back to it
2024-05-15 Refactor
2024-05-15 Fighting still
2024-05-15 Mostly Functional
2024-05-15 Mostly Functional 1
2025-01-29 added ballmouse
2025-02-10 Updating to get ready for the 006
2025-02-10 Started quark
2025-02-14 006 dev board done but for the tweaking
2025-02-19 moar
